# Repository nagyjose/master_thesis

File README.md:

# Diplomová práce – Systém kontrolních stanovišť a osobních jednotek pro orientační sporty

> Komplexní hardwarový a softwarový ekosystém pro měření mezičasů a bezdrátový přenos dat při orientačních a vytrvalostních závodech (orientační běh, MTBO, lyžařský orientační běh). Systém využívá časování a vzájemnou rádiovou komunikaci dle standardu **IEEE 802.15.4**, Bluetooth Low Energy (BLE) pro konfiguraci a servisní odečet, bezdrátové indukční nabíjení standardu Qi a vzdálený přenos mezičasů do závodního centra přes úzkopásmovou síť **NB-IoT** (Narrowband IoT).

**Autor:** Josef Nagy  
**Instituce:** České vysoké učení technické v Praze (Fakulta elektrotechnická)  
**Stav projektu:** Dokončeno a ověřeno (HW Revize 2.1 / FW v1.24) | **Licence:** Open Source / Akademické využití

---

## 1. Účel a řešený problém

Tradiční systémy pro orientační běh vyžadují fyzický kontakt čipu závodníka s kontrolní stanicí (kontaktní ražení) nebo využívají proprietární rádiové protokoly s omezeným dosahem a bez možnosti přímého online přenosu průběžných mezičasů z lesa do cílového prostoru.

Tento projekt přináší moderní modulární řešení:
1. **Základnová kontrolní stanice (Kontrola):** Stacionární jednotka umístěná na kontrolním bodě v terénu. Detekuje průchod závodníků bezkontaktně v rádiovém poli IEEE 802.15.4 (dosah 0.5 až 2 m), zaznamenává přesný čas průchodu s milisekundovou stabilitou (synchronizovaný krystal LSE) a odesílá mezičasy přes celulární síť NB-IoT na server pořadatele.
2. **Osobní jednotka závodníka (Závodník):** Kompaktní, lehká a odolná nositelná jednotka nošená běžcem na ruce, prstu či řídítkách kola. Při průchodu kontrolním bodem provede záznam do interní paměti a poskytne závodníkovi okamžitou akustickou (4 kHz piezo) a vizuální (LED) zpětnou vazbu.
3. **Výrobní a testovací infrastruktura:** Integrovaný technologický panel pro sériové SMT osazení (`production/`) a jehličkový programovací přípravek Bed-of-Nails (`testing/`) pro rychlé nahrání firmwaru a testování.
4. **Hermetické provedení pouzder:** 3D mechanické konstrukce krabiček (`mechanics/`) optimalizované pro venkovní použití s integrovaným Qi bezdrátovým nabíjením eliminujícím vnější konektory.

---

## 2. Systémová architektura

Následující diagram znázorňuje kompletní architekturu celého systému od detekce průběhu až po výrobu a testování:

```mermaid
flowchart TD
    subgraph Runner["🏃 Závodník na trati"]
        Z["Osobní jednotka Závodník<br/>(STM32WB55CGUx + Qi + Bzučák 4 kHz)"]
    end

    subgraph Checkpoint["🚩 Kontrolní stanoviště v terénu"]
        K["Kontrolní stanice Kontrola<br/>(STM32WB55RGVx + Quectel BC660K)"]
    end

    subgraph RF["📡 Bezdrátové rozhraní (RF 2.4 GHz)"]
        Z <== "1. Bezkontaktní detekce & časování<br/>(IEEE 802.15.4 / sub-ms handshake)" ==> K
        Z -. "Konfigurace & odečet (BLE 5.4)" .-> Mobile["Mobilní aplikace pořadatele"]
        K -. "Servisní diagnostika (BLE / USB)" .-> Mobile
    end

    subgraph Feedback["🔊 Zpětná vazba pro běžce"]
        Z --> BUZZ["Akustický bzučák 4 kHz + 💡 Záblesk LED"]
    end

    subgraph Cloud["☁️ Závodní centrum & Online výsledky"]
        K == "2. Online přenos mezičasů (NB-IoT)" ==> Server["Centrální závodní server & Live Tracking"]
        Server --> LiveWeb["Online výsledkový web pro diváky"]
        FinishUnit["Cílová čtečka závodníků"] -. "Vyčtení historie" .-> Server
    end

    subgraph Infrastructure["🏭 Výrobní a testovací infrastruktura (Monorepo DP)"]
        Panel["DP-Panel (production/)<br/>4vrstvý výrobní SMT panel pro JLCPCB"]
        Jig["DP-jigs (testing/)<br/>41pinový Bed-of-Nails testovací přípravek"]
        Mech["DP-Enclosure (mechanics/)<br/>Vodotěsná 3D pouzdra FreeCAD"]
        Panel -. "Vylomení osazených desek" .-> Jig
        Jig -. "Flash firmwaru & testování" .-> K
        Jig -. "Flash firmwaru & testování" .-> Z
        Mech -. "Zapouzdření desek" .-> K
        Mech -. "Zapouzdření desek" .-> Z
    end
```

---

## 3. Struktura repozitáře (Monorepo)

Repozitář sdružuje veškeré zdrojové kódy firmwaru, hardwarové návrhy desek, výrobní panelizaci, testovací přípravky i mechanické modely pouzder:

```text
DP/
├── hardware/
│   ├── DP-Kontrola/            # [PRJ-10] Zdrojový HW návrh kontrolní stanice (KiCad 8/9)
│   │   ├── DP-Kontrola.kicad_pro / kicad_sch / kicad_pcb
│   │   ├── MCU.kicad_sch, NB-IoT-module.kicad_sch, wireless-charger.kicad_sch
│   │   ├── DP-Kontrola-*.gbr / drl / dxf / step (Výrobní a 3D podklady)
│   │   └── README.md           # Podrobná technická dokumentace desky Kontrola
│   └── DP-Zavodnik/            # [PRJ-11] Zdrojový HW návrh osobní jednotky (KiCad 8/9)
│       ├── DP-Zavodnik.kicad_pro / kicad_sch / kicad_pcb
│       ├── MCU.kicad_sch, wireless-charger.kicad_sch, signaling.kicad_sch
│       ├── DP-Zavodnik-*.dxf / step / pdf (Výrobní a 3D podklady)
│       └── README.md           # Podrobná technická dokumentace desky Závodník
│
├── Kontrola_Syst/              # C / HAL Firmware stanice Kontrola (STM32CubeIDE)
│   ├── Core/                   # Aplikační logika (M4): main.c, app_entry.c, RTC, flash logger
│   ├── STM32_WPAN/             # Wireless middleware (M0+): BLE, 802.15.4 MAC, app_nbiot.c
│   ├── Drivers/                # CMSIS a STM32WBxx HAL drivery
│   └── Kontrola_Syst.ioc       # Projekt STM32CubeMX
│
├── Zavodnik_Syst/              # C / HAL Firmware jednotky Závodník (STM32CubeIDE)
│   ├── Core/                   # Aplikační logika (M4): stavový automat, bzučák 4 kHz, LPM
│   ├── STM32_WPAN/             # Bezdrátový zásobník IEEE 802.15.4 a BLE
│   ├── Drivers/                # CMSIS a STM32WBxx HAL drivery
│   └── Zavodnik_Syst.ioc       # Projekt STM32CubeMX
│
├── production/                 # [PRJ-12] Výrobní panelizace plošných spojů (DP-Panel)
│   ├── DP-Panel.kicad_pcb      # Sdružený 4vrstvý výrobní panel (114.05 × 77.55 mm)
│   ├── DP-Panel-job.gbrjob     # Gerber job s definicí stackupu Nan-Ya NP-155FR
│   ├── fab-data/               # Kompletní výrobní balíček (Gerber, BOM s LCSC ID, CPL)
│   └── README.md               # Dokumentace výrobního panelu pro SMT linku
│
├── testing/                    # [PRJ-13] Testovací a flashovací přípravek (DP-jigs)
│   ├── DP-jigs.kicad_pcb / sch # 2vrstvá deska Bed-of-Nails testeru
│   ├── fab-data/               # Výrobní data přípravku pro výrobu
│   └── README.md               # Dokumentace testeru a postup oživování
│
├── mechanics/                  # [PRJ-15] 3D konstrukce krabiček a pouzder (DP-Enclosure)
│   ├── DP-Kontrola.FCStd       # Parametrický 3D model krabičky Kontrola ve FreeCADu
│   ├── *.png                   # 15 fotorealistických renderů pohledů a řezů
│   └── README.md               # Návod na 3D tisk a montáž pouzder
│
├── .gitignore                  # Ochrana před commitem build artefaktů, záloh a cache
└── README.md                   # Tato hlavní přehledová dokumentace monorepa
```

---

## 4. Klíčové hardwarové komponenty a subsystémy

Obě jednotky sdílejí společnou architekturu postavenou na mikrokontrolérech STMicroelectronics a správě napájení Texas Instruments:

| Subsystém | Jednotka Kontrola | Jednotka Závodník |
| :--- | :--- | :--- |
| **Řídící mikrokontrolér** | **STM32WB55RGVx** (VFQFPN68)<br/>Dual Core Cortex-M4 + M0+ | **STM32WB55CGUx** (UFQFPN48)<br/>Kompaktní miniaturní pouzdro |
| **RF komunikace** | 2.4 GHz IEEE 802.15.4 & BLE 5.4,<br/>integrovaná PCB anténa | 2.4 GHz IEEE 802.15.4 & BLE 5.4,<br/>integrovaná PCB anténa |
| **Celulární telemetrie** | **Quectel BC660K-GL** (NB-IoT modem)<br/>externí anténa SMA / u.FL | *Není osazeno (přenos přes Kontrolu)* |
| **Bezdrátové nabíjení** | **TI BQ51013BRHLR** (Qi přijímač 5 W) | **TI BQ51013BRHLR** (Qi přijímač 5 W) |
| **Správa nabíjení & Power-Path** | **TI BQ24232RGTR** (až 500 mA) | **TI BQ24232RGTR** (přizpůsobeno Li-Po) |
| **Hlavní step-down měnič** | **TI TPS62842DGRR** ($I_Q \approx 60\text{ nA}$) | **TI TPS62842DGRR** ($I_Q \approx 60\text{ nA}$) |
| **Napájení modemu** | **TI TPS628502QDRLRQ1** (2 A buck) | *Není přítomno* |
| **Zpětná vazba pro uživatele** | RGB stavové LED, bzučák, USB CDC | Vysoce svítivé LED, 4 kHz piezo driver |
| **Deska plošných spojů** | 4 vrstvy FR4, ENIG zlacení | 4 vrstvy FR4, zaoblený nositelný tvar |

---

## 5. Softwarová architektura a bezdrátový zásobník

Firmware běží na dvoujádrovém mikrokontroléru řady STM32WB:
- **CPU1 (ARM Cortex-M4 @ 64 MHz):** Běh uživatelské aplikace, sekvencer událostí `UTIL_SEQ`, obsluha RTC časovače, správa energetických režimů (Sleep/Stop mode), zápis do Flash paměti (`flash_logger.c`), řízení NB-IoT FIFO fronty a USB komunikace.
- **CPU2 (ARM Cortex-M0+ @ 32 MHz):** Vyhrazený bezdrátový koprocesor. Vyžaduje nahrání binárního firmwaru ST `stm32wb5x_Ble_Mac_802_15_4_fw.bin`. Zajišťuje bezdrátovou obsluhu na nejnižší vrstvě PHY/MAC v reálném čase bez zatížení aplikačního jádra.
- **Mezijádrová komunikace:** Realizována pomocí hardwarového řadiče IPCC (Inter-Processor Communication Controller) a sdílené paměti RAM.

---

## 6. Návod na zprovoznění a vývoj

### A. Vývoj a úprava hardwaru (KiCad)
1. Nainstalujte **KiCad EDA v8.0** nebo novější (testováno i na KiCad 9).
2. Otevřete projekt `hardware/DP-Kontrola/DP-Kontrola.kicad_pro` nebo `hardware/DP-Zavodnik/DP-Zavodnik.kicad_pro`.
3. Všechny knihovny symbolů a footprintů jsou uloženy v projektu nebo odpovídají standardní KiCad knihovně.
4. Výrobní Gerbery a vrtací podklady jsou vygenerovány ve složkách jednotlivých desek a v modulu `production/`.

### B. Překlad firmwaru (STM32CubeIDE)
1. Otevřete **STM32CubeIDE** (testováno na verzi 1.15+).
2. Zvolte `File -> Import... -> Existing Projects into Workspace` a načtěte složky `Kontrola_Syst` a `Zavodnik_Syst`.
3. Před prvním spuštěním nového mikrokontroléru nahrajte do koprocesoru bezdrátový zásobník:
   - Spusťte nástroj **STM32CubeProgrammer**.
   - Připojte desku přes programátor ST-LINK (SWD rozhraní na testovacím přípravku `testing/`).
   - Přejděte na záložku *Firmware Upgrade* a nahrajte binárku `stm32wb5x_Ble_Mac_802_15_4_fw.bin` na vyhrazenou adresu bezdrátového subsystému.
4. Zkompilujte projekt v konfiguraci `Release` nebo `Debug` a nahrajte jej do mikrokontroléru.

### C. Mechanická pouzdra a 3D konstrukce (mechanics/)

Modul `mechanics/` obsahuje kompletní 3D mechanické řešení pouzder a krabiček vyvinutých pro obě jednotky časoměrného systému:

| Pouzdro kontrolní stanice Kontrola | Pouzdro osobní jednotky Závodník |
| :---: | :---: |
|  |  |

Podrobné informace a kompletní fotogalerii viz [mechanics/README.md](file:///c:/Users/josef/Documents/KiCad-projects/DP/mechanics/README.md).

### D. Výrobní panelizace a podklady pro osazení (production/)

Sdružený 4vrstvý technologický panel spojující desky Kontrola a Závodník pro sériové osazování na SMT lince (JLCPCB):

| 3D render výrobního panelu shora | Výrobní layout vrstvy Top Copper (F.Cu) |
| :---: | :---: |
|  |  |

Podrobné informace, vrstvy a kusovník viz [production/README.md](file:///c:/Users/josef/Documents/KiCad-projects/DP/production/README.md).

### E. Programovací a testovací přípravek (testing/)

Dvouvrstvý Bed-of-Nails tester s 41 pružinovými kontakty a rozhraním IDC 2×22 pro oživování, diagnostiku a programování obou desek:

| Schéma zapojení testovacího přípravku | 3D render osazeného testeru Bed-of-Nails |
| :---: | :---: |
|  |  |

Podrobné informace, schéma a montážní výkres viz [testing/README.md](file:///c:/Users/josef/Documents/KiCad-projects/DP/testing/README.md).

---

## 7. Návaznost modulů v rámci diplomové práce

- **PRJ-10 (DP-Kontrola):** Integrováno ve složce `hardware/DP-Kontrola/`.
- **PRJ-11 (DP-Zavodnik):** Integrováno ve složce `hardware/DP-Zavodnik/`.
- **PRJ-12 (DP-Panel):** Integrováno ve složce `production/`.
- **PRJ-13 (DP-jigs):** Integrováno ve složce `testing/`.
- **PRJ-14 (DP-Frame):** Vyřazeno / nepublikováno (prázdná šablona bez zapojení a DPS).
- **PRJ-15 (DP-Enclosure):** Integrováno ve složce `mechanics/`.
- **PRJ-16 (DP-Merge):** Vyřazeno / nepublikováno (prázdná schránka).

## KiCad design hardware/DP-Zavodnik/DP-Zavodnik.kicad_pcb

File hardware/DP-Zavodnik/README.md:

# DP-Zavodnik – Hardwarová osobní jednotka závodníka

> Hardwarový návrh kompaktní 4vrstvé desky plošných spojů osobní jednotky pro bezkontaktní časomíru orientačních sportů (nositelné zařízení na ruku, prst či řídítka kola) s mikrokontrolérem STM32WB55, integrovanou RF anténou 2.4 GHz (IEEE 802.15.4 / BLE), akusticko-optickou odezvou a bezdrátovým Qi nabíjením.

**Stav projektu:** Dokončeno (HW Revize 1.0) | **Hlavní technologie:** KiCad 8/9, STM32WB55CGUx (UFQFPN48, Dual-core ARM Cortex-M4 + M0+), Texas Instruments Power Management (BQ51013B, BQ24232, TPS62842)

---

## 1. Účel a funkce

Projekt **DP-Zavodnik** představuje osobní mobilní jednotku (obdoba moderního elektronického čipu SI-Card / SIAC) v systému bezkontaktní časomíry pro orientační sporty. Závodník jednotku nese během celého závodu upevněnou na prstu, zápěstí nebo na rámu kola (MTBO). 

Hlavní funkce zařízení:
- **Bezkontaktní ražení kontrol (Air Punching):** Automatická detekce kontrolního stanoviště [DP-Kontrola](../DP-Kontrola) při průběhu v rádiovém dosahu pomocí standardu IEEE 802.15.4 bez nutnosti fyzického zasouvání čipu do otvoru.
- **Okamžitá odezva (Feedback):** Výkonný akustický bzučák buzený signálem 4 kHz a vysoce svítivé LED diody dávají závodníkovi v plném běhu okamžité a zřetelné potvrzení úspěšného zaznamenání kontrolního bodu.
- **Nenulová paměť závodu:** Ukládání identifikačních kódů kontrol a přesných časů oražení do interní paměti mikrokontroléru pro následné vyčtení v cílovém prostoru.
- **Ergonomická nositelná konstrukce:** Zaoblený tvar desky přizpůsobený tělu závodníka a integraci do kompaktního pouzdra [DP-Enclosure](../../mechanics).
- **Hermetické provedení a Qi nabíjení:** Zařízení nemá vnější kontakty podléhající oxidaci a znečištění blátem či potem; nabíjení vestavěného Li-Po článku probíhá bezdrátově přes standard Qi.

---

## 2. Architektura a blokové schéma

Schéma zapojení je optimalizováno pro minimální rozměry, nízkou hmotnost a maximální výdrž na jedno nabití.

```mermaid
flowchart TD
    subgraph Power["⚡ Napájecí subsystém"]
        Qi["Bezdrátové Qi nabíjení<br/>(TI BQ51013B)"] -->|5V rect| BQ["Li-Po Charger & Power Path<br/>(TI BQ24232)"]
        USB["USB rozhraní<br/>(Servis / nouzové nabíjení)"] --> BQ
        BAT["Li-Po akumulátor<br/>(3.7V jednocelový)"] <--> BQ
        BQ -->|VSYS| REG["Ultra-Low-Iq Buck 3.3V<br/>(TI TPS62842, Iq=60nA)"]
    end

    subgraph Core["🧠 Řídící & RF jádro"]
        REG --> MCU["STM32WB55CGUx<br/>(UFQFPN48, Dual-core<br/>Cortex-M4 + Cortex-M0+)"]
        MCU <--> RF_ANT["Integrovaná PCB anténa 2.4 GHz<br/>(IEEE 802.15.4 / BLE)"]
        MCU --> RTC["RTC krystal 32.768 kHz (LSE)"]
        MCU --> HSE["Vysokofrekvenční krystal 32 MHz (HSE)"]
    end

    subgraph UserFeedback["🔊 Signalizace a odezva"]
        MCU -->|PWM 4 kHz driver| BUZZ["Piezoelektrický bzučák<br/>(Akustické potvrzení oražení)"]
        MCU --> LEDS["Optická LED indikace<br/>(Zelená / Červená / Modrá)"]
        BAT -.->|ADC monitor| MCU
    end
```

---

## 3. Hardware, schéma a PCB

### 3.1 3D vizualizace osobní jednotky

### 3.2 Schéma zapojení

<details>
<summary>🔍 Zobrazit detailní listy schématu zapojení (strany 2–4)</summary>

#### List 2: Mikrokontrolér STM32WB55CGUx, oscilátory a RF výstup

#### List 3: Qi bezdrátové nabíjení (BQ51013B) a Power-Path správa baterie (BQ24232)

#### List 4: Budicí obvod 4 kHz piezo bzučáku, stavové LED a monitorování akumulátoru

</details>

📄 [Otevřít kompletní schéma v plném rozlišení (vektorové PDF)](DP-Zavodnik-Schema.pdf)

### 3.3 Návrh a layout plošného spoje (PCB Layout)

<details>
<summary>🔍 Zobrazit výkresy jednotlivých vrstev a technologických masek</summary>

| Vrstva / Náhled | Soubor |
| :--- | :--- |
| **Top strana (F.Cu + Silk + Mask)** |  |
| **Vnitřní vrstva In1 (GND / Power)** |  |
| **Vnitřní vrstva In2 (Signály)** |  |
| **Bottom strana (B.Cu)** |  |
| **Pájecí maska a potisk** |  |
| **Vrtací plán (Drill drawing)** |  |
| **Kompletní montážní výkres** |  |

</details>

📄 [Otevřít kompletní výrobní výkres vrstev v plném rozlišení (vektorové PDF)](DP-Zavodnik-Layout.pdf)

---

## 4. Struktura projektu

```text
DP-Zavodnik/
├── docs/
│   └── images/                 # Exportované grafické náhledy schémat, vrstev layoutu a 3D rendery
│       ├── pcb_3d_render.png   # 3D fotorealistický render osazené jednotky
│       ├── pcb_layout*.png     # Náhledy vrstev a masek plošného spoje
│       └── schematic_p*.png    # Náhledy všech 4 listů schématu
├── DP-Zavodnik.kicad_pro       # Hlavní projektový soubor KiCad
├── DP-Zavodnik.kicad_sch       # Kořenové schéma (Sheet 1)
├── MCU.kicad_sch               # Schéma zapojení mikrokontroléru STM32WB55CGUx (Sheet 2)
├── wireless-charger.kicad_sch  # Schéma Qi bezdrátového nabíjení a Power-Path (Sheet 3)
├── signaling.kicad_sch         # Schéma driveru bzučáku, LED diod a měření baterie (Sheet 4)
├── DP-Zavodnik.kicad_pcb       # 4vrstvá deska plošných spojů s optimalizovaným tvarem
├── DP-Zavodnik-Base.step       # 3D STEP model spodní části desky
├── DP-Zavodnik-Lid.step        # 3D STEP model krytu/sestavy
├── DP-Zavodnik-Layout.pdf      # Výrobní výkres vrstev DPS v PDF
├── DP-Zavodnik-Schema.pdf      # Vektorové schéma v PDF
├── DP-Zavodnik-*.dxf           # Exporty vrstev do formátu DXF pro mechanickou konstrukci
├── DP-Zavodnik-view-*.png      # Fotorealistické 3D rendery osazené desky
└── .gitignore                  # Ochrana před zálohami, kolizními soubory a cache KiCadu
```

---

## 5. Technické parametry hardwaru

| Parametr | Hodnota / Specifikace |
| :--- | :--- |
| **Rozměry a tvar** | Miniaturní zaoblená deska optimalizovaná pro tělo sportovce |
| **Počet vrstev** | 4 vrstvy (Top Signal, In1 Power/GND, In2 Signal, Bottom Signal) |
| **Materiál a tloušťka** | FR4, 1.6 mm, povrchová úprava ENIG (zlacení) |
| **Mikrokontrolér** | **STM32WB55CGUx** (UFQFPN48, dual-core Cortex-M4 @ 64 MHz + Cortex-M0+ pro RF) |
| **RF rozhraní 2.4 GHz** | Integrovaná mikropásková anténa, LC filtr, IEEE 802.15.4 & BLE 5.4 |
| **Bezdrátové nabíjení** | **TI BQ51013BRHLR** – certifikovaný přijímač Qi standardu |
| **Správa napájení a nabíjení** | **TI BQ24232RGTR** – lineární nabíječ s dynamickým řízením napájení |
| **Step-down napájení** | **TI TPS62842DGRR** – ultra-low IQ měnič pro maximalizaci výdrže akumulátoru |
| **Akustická odezva** | Piezo měnič řízený diskrétním MOSFET budičem na rezonanční frekvenci 4 kHz |
| **Optická odezva** | Vysoce svítivé signalizační LED diody |
| **Napájení** | Integrovaný miniaturní Li-Po článek (3.7 V) |

---

## 6. Požadavky a otevření projektu

- **KiCad EDA:** Doporučena verze **8.0** nebo novější (projekt vytvořen a verifikován v KiCad 8/9).
- Pro otevření projektu spusťte `DP-Zavodnik.kicad_pro` v KiCadu.
- Výrobní předlohy jednotlivých vrstev jsou k dispozici v souborech `DP-Zavodnik-Layout.pdf` a DXF exportech.
- Pro návrh plastové krabičky a montážních prvků použijte 3D STEP modely `DP-Zavodnik-Base.step` a `DP-Zavodnik-Lid.step`.

---

## 7. Vazby na další projekty

- **[DP-Kontrola](../DP-Kontrola) (PRJ-10):** Základnová stacionární stanice, která zaznamenává průchod této jednotky.
- **[DP Monorepo](https://github.com/nagyjose/DP):** Centrální repozitář obsahující firmware `Zavodnik_Syst` a `Kontrola_Syst`.
- **[DP-Panel](../../production) (PRJ-12):** Společná panelizace s deskou Kontrola pro hromadné osazování.
- **[DP-jigs](../../testing) (PRJ-13):** Testovací a flashovací přípravek pro nahrání firmwaru na výrobní lince.
- **[DP-Enclosure](../../mechanics) (PRJ-15):** 3D model pouzdra navržený ve FreeCADu.

---

## 8. Stav projektu a historie

- **Verze 1.0 (Diplomová práce - Finální):** Kompletně navržený hardware, vyrobené prototypové desky, ověřena funkčnost bezdrátového nabíjení, 4 kHz bzučáku i oboustranné rádiové komunikace 802.15.4 s jednotkou Kontrola.

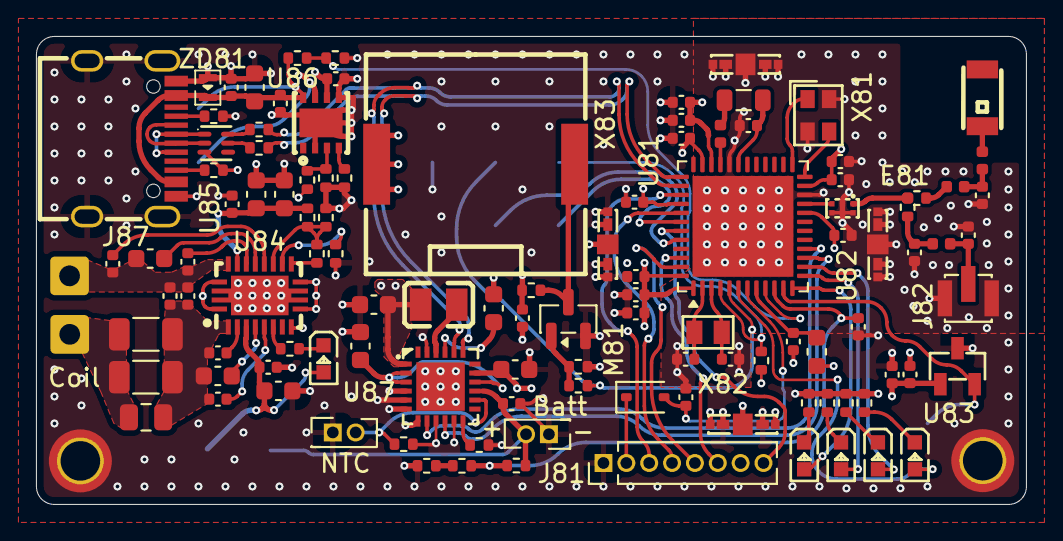
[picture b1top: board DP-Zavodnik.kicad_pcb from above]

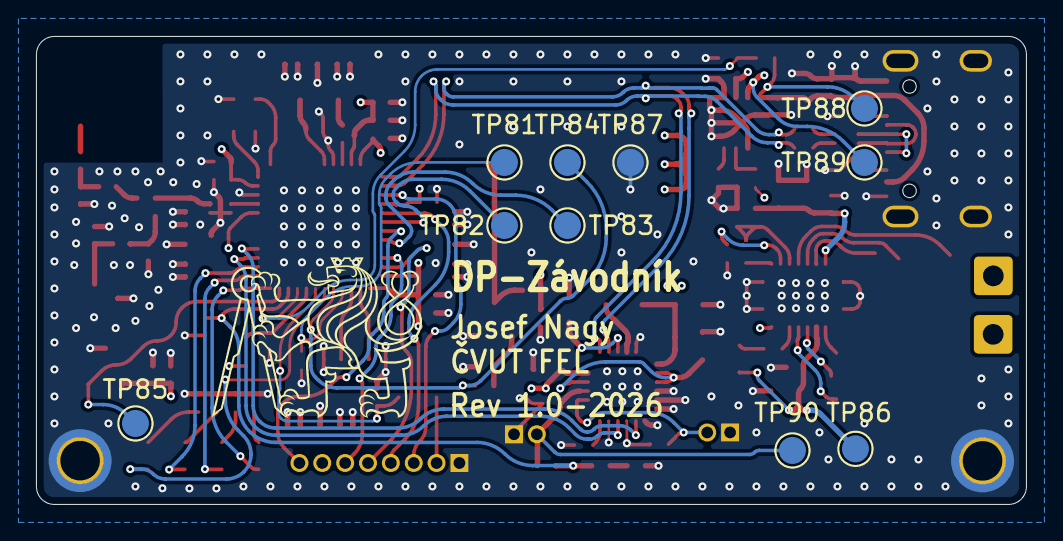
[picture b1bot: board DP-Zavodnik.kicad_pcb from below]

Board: 4 copper layers, 55.0 x 26.0 mm, 125 parts (10 on the bottom side), 78 nets.

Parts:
C81, C84, C86, C87, C88, C90, C92, C93, C95, C99, C100, C102, C114, C116, C121, C122: 100n; C_0402_1005Metric
C82, C83, C85, C101: 4.7u; C_0402_1005Metric
C89, C119: 100p; C_0402_1005Metric
C91, C94: 7.5p; C_0402_1005Metric
C96, C97, C98: N.C.; C_0402_1005Metric
C103: C_0805_2012Metric
C104, C105: 39n; C_1206_3216Metric
C106: 910p; C_0402_1005Metric
C107: C_0402_1005Metric
C108, C113: 470n; C_0603_1608Metric
C109, C112: 22n; C_0402_1005Metric
C110, C111: 10n; C_0402_1005Metric
C115, C117, C118, C124, C125, C126: 10u; C_0603_1608Metric
C120: 4.7u; C_0603_1608Metric
C123: 1u; C_0402_1005Metric
C127: 2.2u; C_0603_1608Metric
D81: 1N5819WS; D_SOD-323
E81: 2450AT18B100E; ANT-SMD_L3.2-W1.6
FB81: BLM18AG601SN1D; L_0603_1608Metric
H81, H82: MountingHole_Pad; MountingHole_2.2mm_M2_ISO7380_Pad_TopBottom
J81: Conn_01x08; PinHeader_1x08_P1.27mm_Vertical
J82: CONUFL001-SMD-T; IPEX-SMD_3P-L2.6-W2.6-LS3.0
J85, J86: SolderWire-0.5sqmm_1x01_D0.9mm_OD2.1mm
J87: TYPE-C-31-M-12; USB-C_SMD-TYPE-C-31-M-12_1
J88, J90: Conn_01x02; PinHeader_2x01_P1.27mm_Vertical
L81: 10n; L_0402_1005Metric
L82: 10u; L_0805_2012Metric
L83, L84, L85: 0R; L_0402_1005Metric
L87: 2.2u; L0806
LED81: VLMO1300-GS08; LED0603-RD_BLUE
LED82: VLMS1300-GS08; LED0603-RD_BLUE
LED83: VLMG1300-GS08; LED0603-RD_BLUE
LED84, LED85: VLMB1300-GS08; LED0603-RD_BLUE
M81: 2N7002; SOT-23
R81, R85, R97, R109: 10k; R_0402_1005Metric
R82, R83, R103, R104: 0R; R_0402_1005Metric
R84: 100R; R_0402_1005Metric
R86, R96: 1k; R_0402_1005Metric
R87, R88, R89: 1M; R_0402_1005Metric
R90, R91, R105: 100k; R_0402_1005Metric
R92, R93, R94, R95: 200R; R_0402_1005Metric
R98: 1.37k; R_0402_1005Metric
R99: 20k; R_0402_1005Metric
R100: 196R; R_0402_1005Metric
R101, R102: 5.1k; R_0402_1005Metric
R106: 22k; R_0402_1005Metric
R107: 470R; R_0402_1005Metric
R108: 4.7k; R_0402_1005Metric
SC81, SC82, SC83, SC84: S0951-46R; SMD_S0951-46R_1
TP81, TP82, TP83, TP84, TP85, TP86, TP87, TP88, TP89, TP90: TestPoint_Pad_D1.5mm
U81: STM32WB55CGUx; QFN-48-1EP_7x7mm_P0.5mm_EP5.6x5.6mm
U82: MLPF-WB55-01E3; FILTER-SMD_6P-L1.6-W1.0-P0.50-BL
U83: DRV5032FADBZR; SOT-23-3_L2.9-W1.3-P0.95-LS2.4-BR
U84: BQ51013BRHLR; VQFN-20_L4.5-W3.5-P0.50-BL-EP_BQ24100RHLR
U85: ECMF02-2AMX6; UFQFN-6_L1.7-W1.5
U86: TPS2113ADRBR; SON-8_L3.0-W3.0-P0.65-LS3.0-BL-EP
U87: NPM1100-QDAA-R7; VQFN-24_L4.0-W4.0-P0.50-TL-EP2.7
X81: NX2016SA-32MHZ-STD-CZS-5; OSC-SMD_4P-L2.0-W1.6-BL
X82: NX2012SA-32_768KHZ-EXS00A-MU00527; CRYSTAL-SMD_L2.0-W1.2
X83: PKLCS1212E4001-R1; BUZ-SMD_2P-L12.0-W12.0-L_PKLCS1212E4001-R1
ZD81: ESDA7P60-1U1M; D1610-RD

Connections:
+3V3: C83.1, C84.1, C85.1, C86.1, C87.1, C88.1, C89.1, C90.1, C92.1, C93.1, C100.1, C101.1, C102.1, C124.1, FB81.1, J81.7, L87.1, R86.2, U81.1 (VBAT), U81.20 (VDD), U81.23 (VDDRF), U81.34 (VDDSMPS), U81.35 (VDD), U81.40 (VDDUSB), U81.48 (VDD), U83.1 (VCC), U87.1 (VOUTB), X83.1 (+)
+5VD: C127.1, TP89.1, U86.7 (OUT), U87.17 (VBUS)
+5VL: C114.1, C115.1, C122.1, LED85.2 (+), TP86.1, U84.4 (OUT), U86.6 (IN2)
+5VP: C119.1, C120.1, C121.1, J87.A4B9 (VBUS), J87.B4A9 (VBUS), R90.2, R105.2, TP88.1, U84.9 (AD), U86.8 (IN1), ZD81.1 (C)
/BLE-RF/rf1: R82.1, R83.1, U82.1 (OUT)
/BLE-RF/rf2: L83.1, R82.2
/BLE-RF/rf3: C97.1, L83.2, L85.1
/BLE-RF/rf4: E81.1 (FEED), L85.2
/BLE-RF/rf5: C96.1, L84.1, R83.2
/BLE-RF/rf6: C98.1, J82.1, L84.2
/MCU/nrst: D81.1 (K), J81.2
/MCU/smps: L81.1, L82.2
/power-management/USB-plug/cc1: J87.A5 (CC1), R101.2
/power-management/USB-plug/cc2: J87.B5 (CC2), R102.2
/power-management/USB-plug/d1n: J87.A7 (DN1), J87.B7 (DN2), U85.2 (D-)
/power-management/USB-plug/d1p: J87.A6 (DP1), J87.B6 (DP2), U85.1 (D+)
/power-management/USB-plug/d2n: R104.1, U85.5 (D-)
/power-management/USB-plug/d2p: R103.1, U85.6 (D+)
/power-management/power-switch/ilim2: R107.2, U86.4 (ILIM)
/power-management/power-switch/vsns: R105.1, R106.2, U86.3 (VSNS)
/power-management/regulator/dec: C126.1, U87.21 (DEC)
/power-management/regulator/ichg: R108.2, U87.12 (ICHG)
/power-management/regulator/sw: L87.2, U87.22 (SW)
/power-management/regulator/vsys: C125.1, U87.2 (VOUTBSET1), U87.3 (VOUTBSET0), U87.16 (VSYS)
/power-management/wireless-charger/ac1a: C103.1, C104.1, C105.1, J85.1
/power-management/wireless-charger/fod: R98.1, R99.1, R100.1, U84.14 (FOD)
/power-management/wireless-charger/ilim: R98.2, U84.12 (ILIM)
/power-management/wireless-charger/led5: LED85.1 (-), R96.2
/power-management/wireless-charger/led6: R96.1, U84.7 (/CHG)
/power-management/wireless-charger/rect: C116.1, C117.1, C118.1, R99.2, U84.18 (RECT)
/power-management/wireless-charger/ts: R97.2, U84.13 (TS/CTRL)
/signaling/bz1: M81.1 (G), R84.1, R85.2
/signaling/bz2: M81.3 (D), R86.1, X83.2 (-)
/signaling/led1: LED81.1 (-), R92.2
/signaling/led2: LED82.1 (-), R93.2
/signaling/led3: LED83.1 (-), R94.2
/signaling/led4: LED84.1 (-), R95.2
/signaling/meas: R88.1, R89.2
AC1: C103.2, C104.2, C105.2, C106.1, C107.1, C108.1, C109.1, C110.1, U84.2 (AC1)
AC2: C106.2, C107.2, C111.1, C112.1, C113.1, J86.1, U84.19 (AC2)
BATT_MEAS: C99.1, R87.1, R88.2, U81.10 (ADC1_IN6)
BOOT1: C110.2, U84.3 (BOOT1)
BOOT2: C111.2, U84.17 (BOOT2)
CLAMP1: C108.2, U84.5 (CLMP1)
CLAMP2: C113.2, U84.16 (CLMP2)
COMM1: C109.2, U84.6 (COM1)
COMM2: C112.2, U84.15 (COM2)
GND: C81.2, C82.2, C83.2, C84.2, C85.2, C86.2, C87.2, C88.2, C89.2, C90.2, C91.2, C92.2, C93.2, C94.2, C95.2, C96.2, C97.2, C98.2, C99.2, C100.2, C101.2, C102.2, C114.2, C115.2, C116.2, C117.2, C118.2, C119.2, C120.2, C121.2, C122.2, C123.2, C124.2, C125.2, C126.2, C127.2, H81.1, H82.1, J81.1, J82.2, J82.3, J87.1 (EH), J87.2 (EH), J87.3 (EH), J87.4 (EH), J87.A1B12 (GND), J87.B1A12 (GND), J88.1, J90.1, M81.2 (S), R81.2, R85.1, R89.1, R91.1, R92.1, R93.1, R94.1, R95.1, R97.1, R100.2, R101.1, R102.1, R106.1, R107.1, R108.1, R109.1, SC81.1, SC81.2, SC81.3, SC81.4, SC81.5, SC82.1, SC82.2, SC82.3, SC82.4, SC82.5, SC83.1, SC83.2, SC83.3, SC83.4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
HAL_WKUP: TP85.1, U81.11 (SYS_WKUP4), U83.2 (OUT)
SIG_Blink: LED81.2 (+), U81.6 (PB9)
SIG_Buzzer: R84.2, TP84.1, U81.5 (TIM16_CH1)
SIG_LED1: LED82.2 (+), U81.12 (PA3)
SIG_LED2: LED83.2 (+), U81.13 (PA4)
SIG_LED3: LED84.2 (+), U81.14 (PA5)
SRM32_JTRST: TP83.1, U81.44 (SYS_JTRST)
STM32_BOOT0: R81.1, TP81.1, U81.4 (PH3)
STM32_DN: R104.2, U81.37 (USB_DM), U87.19 (D-)
STM32_DP: R103.2, U81.38 (USB_DP), U87.20 (D+)
STM32_JTDI: TP82.1, U81.42 (SYS_JTDI)
STM32_JTDO: J81.8, U81.43 (SYS_JTDO-SWO)
STM32_NRST: C81.1, D81.2 (A), U81.7 (NRST)
STM32_OSC32_IN: C91.1, U81.2 (RCC_OSC32_IN), X82.1 (OSC1)
STM32_OSC32_OUT: C94.1, U81.3 (RCC_OSC32_OUT), X82.2 (OSC2)
STM32_OSC_IN: U81.25 (OSC_IN), X81.1
STM32_OSC_OUT: U81.24 (OSC_OUT), X81.3
STM32_RF1: U81.21 (RF1), U82.3 (IN)
STM32_RX: J81.5, U81.47 (USART1_RX)
STM32_SMPS_FB: C82.1, L82.1, U81.31 (VFBSMPS)
STM32_SMPS_LX: L81.2, U81.33 (VLXSMPS)
STM32_SWCLK: J81.4, U81.41 (SYS_JTCK-SWCLK)
STM32_SWDIO: J81.3, U81.39 (SYS_JTMS-SWDIO)
STM32_TX: J81.6, U81.46 (USART1_TX)
USB_TRIG: R90.1, R91.2, U81.9 (SYS_WKUP1)
VBAT: C123.1, J88.2, R87.2, TP90.1, U87.15 (VBAT)
VDDA: C95.1, FB81.2, U81.8 (VDDA)
nPM_CHG: U81.16 (PA7), U87.8 (CHG)
nPM_ERR: U81.15 (PA6), U87.10 (ERR)
nPM_NTC: J90.2, R109.2, U87.14 (NTC)

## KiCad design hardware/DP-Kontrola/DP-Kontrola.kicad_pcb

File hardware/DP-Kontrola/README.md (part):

# DP-Kontrola – Hardwarová základnová jednotka časomíry

> Hardwarový návrh 4vrstvé desky plošných spojů stacionární kontrolní stanice pro bezkontaktní časomíru orientačního běhu s dvoujádrovým bezdrátovým mikrokontrolérem STM32WB55, integrovanou RF anténou 2.4 GHz, NB-IoT konektivitou pro online přenos mezičasů do centra závodu a bezdrátovým Qi nabíjením.

**Stav projektu:** Dokončeno (HW Revize 2.1) | **Hlavní technologie:** KiCad 8/9, STM32WB55RGV6 (Dual-core ARM Cortex-M4 + M0+), Quectel BC660K-GL (NB-IoT), Texas Instruments Power Management (BQ51013B, BQ24232, TPS62842)

---

## 1. Účel a funkce

Projekt **DP-Kontrola** tvoří základnovou (stacionární) stanici komplexního systému bezkontaktní časomíry pro orientační sporty (orientační běh, MTBO, běh na lyžích). Stanice je umístěna v terénu na kontrolním stanovišti (lampionu) a plní následující funkce:

- **Bezkontaktní detekce závodníka:** Využívá radiové rozhraní 2.4 GHz na protokolu IEEE 802.15.4 a Bluetooth Low Energy (BLE) pro spolehlivou registraci průběhu závodníka s osobní jednotkou [DP-Zavodnik](../DP-Zavodnik).
- **Přesné měření času:** Synchronizovaný vnitřní RTC obvod s teplotně kompenzovaným krystalem LSE zajišťuje záznam času průchodu s milisekundovou přesností.
- **Online přenos mezičasů (NB-IoT):** Integrovaný celulární modul Quectel BC660K-GL odesílá průchody závodníků v reálném čase přes úzkopásmovou síť IoT do centrálního vyhodnocovacího systému.
- **Autonomní napájení a bezdrátové nabíjení:** Možnost dobíjení Li-Ion/Li-Po článku bez nutnosti otevírání vodotěsné krabičky prostřednictvím bezdrátového Qi rozhraní (5 W) nebo USB-C konektoru s automatickým řízením napájecí cesty (Power Path).
- **Offline záznam a bezpečnost dat:** Zálohování všech oražení do interní Flash paměti pro případ výpadku mobilního signálu v hlubokém lese.

---

## 2. Architektura a blokové schéma

Deska je navržena s důrazem na minimální klidovou spotřebu energie v terénu a vysokou spolehlivost radiového přenosu.

```mermaid
flowchart TD
    subgraph Power["⚡ Napájecí subsystém"]
        Qi["Bezdrátové Qi nabíjení<br/>(TI BQ51013B)"] -->|5V rect| BQ["Li-Ion Charger & Power Path<br/>(TI BQ24232)"]
        USB["USB-C konektor<br/>(5V VBUS)"] --> BQ
        BAT["Li-Ion / Li-Po akumulátor<br/>(3.7V nom)"] <--> BQ
        BQ -->|VSYS| REG_MCU["Ultra-Low-Iq Buck 3.3V<br/>(TI TPS62842, Iq=60nA)"]
        BQ -->|VSYS| REG_NBIOT["High-Current Buck 3.8V<br/>(TI TPS628502)"]
    end

    subgraph Core["🧠 Řídící & RF jádro"]
        REG_MCU --> MCU["STM32WB55RGVx<br/>(ARM Cortex-M4 @ 64MHz<br/>+ Cortex-M0+ pro RF)"]
        MCU <--> RF_ANT["Integrovaná PCB anténa 2.4 GHz<br/>(IEEE 802.15.4 / BLE)"]
        MCU --> RTC["RTC krystal 32.768 kHz (LSE)"]
        MCU <--> USB_DATA["USB 2.0 FS rozhraní<br/>(CDC konfigurace)"]
    end

    subgraph Peripherals["📡 Periferie a telemetrie"]
        REG_NBIOT --> NBIOT["Quectel BC660K-GL<br/>(NB-IoT modem)"]
        MCU <-->|UART + Ri / Wakeup| NBIOT
        NBIOT --> ANT_NBIOT["NB-IoT anténní konektor (u.FL / SMA)"]
        MCU --> LEDS["Optická signalizace (RGB LED)"]
        MCU --> BUZZ["Akustický bzučák"]
        BAT -.->|Dělič napětí / ADC| MCU
    end
```

---

## 3. Hardware, schéma a PCB

### 3.1 3D vizualizace a osazení desky

### 3.2 Schéma zapojení

<details>
<summary>🔍 Zobrazit detailní listy schématu zapojení (strany 2–5)</summary>

#### List 2: Mikrokontrolér STM32WB55, krystaly HSE/LSE a USB

#### List 3: Celulární modem Quectel BC660K-GL a SIM slot

#### List 4: Bezdrátové Qi nabíjení (BQ51013B) a nabíječ baterie (BQ24232)

#### List 5: Signalizace (RGB LED, bzučák) a monitorování napětí baterie

</details>

📄 [Otevřít kompletní schéma v plném rozlišení (vektorové PDF)](DP-Kontrola-Schema.pdf)

### 3.3 Návrh plošného spoje (PCB Layout)

📄 [Otevřít výrobní dokumentaci DPS v plném rozlišení (vektorové PDF)](DP-Kontrola.pdf)

---

## 4. Struktura projektu

```text
DP-Kontrola/
├── docs/
│   └── images/                 # Exportované grafické náhledy schémat, layoutu a 3D rendery
│       ├── pcb_3d_render.png   # 3D fotorealistický render osazené desky
│       ├── pcb_layout.png      # Náhled vrstev plošného spoje
│       └── schematic_p*.png    # Náhledy všech 5 listů schématu
├── DP-Kontrola.kicad_pro       # Hlavní projektový soubor KiCad
├── DP-Kontrola.kicad_sch       # Kořenové schéma (Sheet 1)
├── MCU.kicad_sch               # Schéma MCU části, hodin a krystalů (Sheet 2)
├── NB-IoT-module.kicad_sch     # Schéma modemu Quectel BC660K-GL a SIM slotu (Sheet 3)
├── wireless-charger.kicad_sch  # Schéma Qi cívky, BQ51013B a BQ24232 (Sheet 4)
├── signaling.kicad_sch         # Schéma LED indikace, bzučáku a monitoru baterie (Sheet 5)
├── DP-Kontrola.kicad_pcb       # 4vrstvá deska plošných spojů
├── DP-Kontrola-base.step       # 3D STEP model spodní části desky
├── DP-Kontrola-lid.step        # 3D STEP model krytu/sestavy
├── DP-Kontrola.pdf             # Kompletní výrobní dokumentace v PDF
├── DP-Kontrola-Schema.pdf      # Všechny listy schématu ve vektorovém PDF
├── DP-Kontrola-Layout-*.pdf    # Výkresy jednotlivých vrstev DPS
├── DP-Kontrola-*.dxf           # Exporty vrstev do formátu DXF pro mechanickou konstrukci
├── DP-Kontrola-*.gbr / drl     # Výrobní Gerbery a vrtací data (drill)
├── DP-Kontrola-view-*.png      # 3D fotorealistické rendery osazené desky
└── .gitignore                  # Ochrana před zálohami a cache soubory KiCadu
```

---

## 5. Technické parametry hardwaru

| Parametr | Hodnota / Specifikace |
| :--- | :--- |
| **Rozměry DPS** | Kompaktní tvar přizpůsobený skříňce [DP-Enclosure](../../mechanics) |
| **Počet vrstev** | 4 vrstvy (Top Signal, In1 Power/GND, In2 Signal, Bottom Signal) |
| **Materiál a tloušťka** | FR4, 1.6 mm, povrchová úprava ENIG (zlacení) |
| **Mikrokontrolér** | **STM32WB55RGVx** (VFQFPN68, dual-core Cortex-M4 + Cortex-M0+) |
| **RF rozhraní 2.4 GHz** | Integrovaná mikropásková anténa, LC přizpůsobovací obvod, IEEE 802.15.4 & BLE 5.4 |
| **Celulární konektivita** | **Quectel BC660K-GL** (pásma B1, B3, B5, B8, B20, B28), nanoSIM / eSIM slot |
| **Bezdrátové nabíjení** | **TI BQ51013BRHLR** – certifikovaný přijímač Qi v1.2 (až 5 W) |
| **Správa napájení a baterie** | **TI BQ24232RGTR** – lineární nabíječ Li-Ion/Li-Po s dynamickým Power-Path |
| **Napájení MCU větve** | **TI TPS62842DGRR** – ultra-low IQ synchronní step-down měnič ($I_Q \approx 60\text{ nA}$) |
| **Napájení modemu** | **TI TPS628502QDRLRQ1** – 2A synchronní step-down měnič dimenzovaný na proudové špičky NB-IoT |
| **Uživatelské rozhraní** | RGB LED stavová signalizace, piezoelektrický bzučák, servisní USB-C rozhraní |

---

## 6. Požadavky a otevření projektu

- **KiCad EDA:** Doporučena verze **8.0** nebo vyšší (projekt byl vytvořen a verifikován v KiCad 8/9).
- Pro otevření projektu otevřete soubor `DP-Kontrola.kicad_pro` v prostředí KiCad.
- Pro výrobu DPS jsou přímo v kořenové složce připraveny výrobní soubory Gerber (`DP-Kontrola-*.gbr`) a vrtací soubory Excellon (`*.drl`).
- Pro mechanickou integraci do pouzdra jsou k dispozici modely `DP-Kontrola-base.step` a `DP-Kontrola-lid.step`.

---

## 7. Vazby na další projekty

Projekt je pevnou součástí ekosystému diplomové práce:

- **[DP-Zavodnik](../DP-Zavodnik) (PRJ-11):** Párová mobilní jednotka závodníka, se kterou kontrola komunikuje protokolem 802.15.4.
- **[DP Monorepo](https://github.com/nagyjose/DP):** Centrální repozitář obsahující firmware obou jednotek (`Kontrola_Syst`, `Zavodnik_Syst`).
- **[DP-Panel](../../production) (PRJ-12):** Panelizovaná výrobní předloha sdružující desky Kontrola a Závodník do jednoho výrobního přířezu.
- **[DP-jigs](../../testing) (PRJ-13):** Jehličkový programovací a testovací přípravek (pogo-pin bed-of-nails) pro oživování této desky.
- **[DP-Enclosure](../../mechanics) (PRJ-15):** 3D model vodotěsného plastového pouzdra navržený ve FreeCADu.

---

## 8. Stav projektu a historie

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
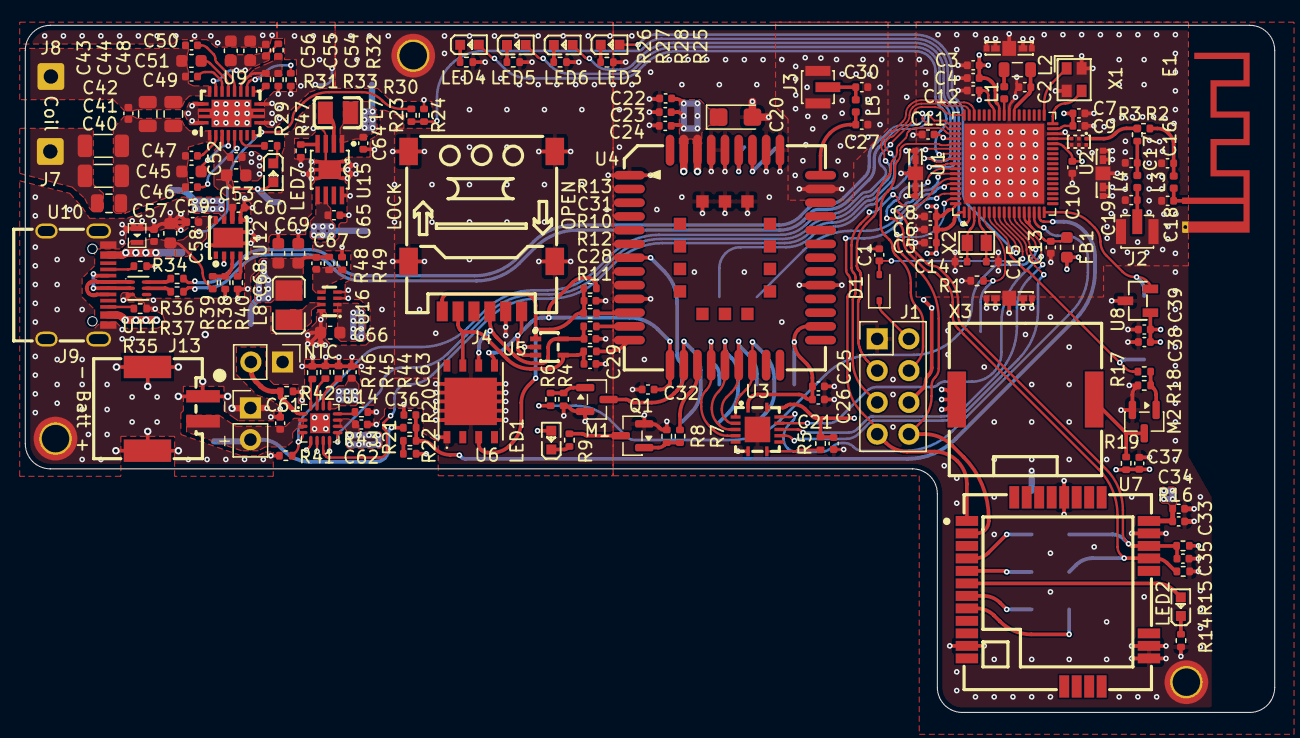
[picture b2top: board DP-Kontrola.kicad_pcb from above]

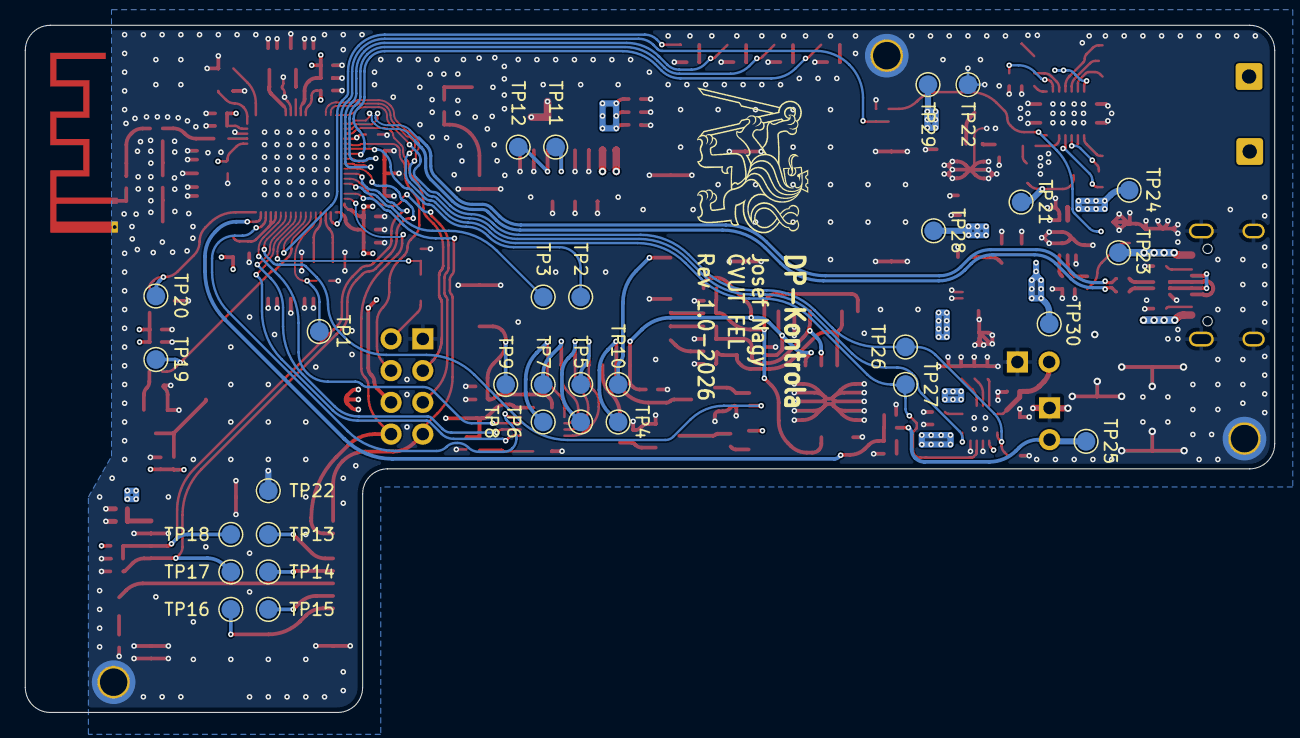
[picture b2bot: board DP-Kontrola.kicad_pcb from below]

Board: 4 copper layers, 100.0 x 55.0 mm, 204 parts (31 on the bottom side), 121 nets.

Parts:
C1, C4, C6, C7, C8, C10, C11, C12, C13, C21, C22, C25, C32, C34, C35, C36, C37, C39, C52, C54, C59, C60: 100n; C_0402_1005Metric
C2, C3, C5, C26, C33, C38, C61, C62, C63, C65: 4.7u; C_0402_1005Metric
C9, C23, C43, C57: 100p; C_0402_1005Metric
C14, C15: 7.5p; C_0402_1005Metric
C16, C17, C18, C19, C27, C30: N.C.; C_0402_1005Metric
C20: 100u; CP_EIA-3216-18_Kemet-A
C24: 22p; C_0402_1005Metric
C28, C29, C31: 33p; C_0402_1005Metric
C40, C48: N.C.; C_0805_2012Metric
C41, C42: 100n; C_1206_3216Metric
C44: 2.2n; C_0805_2012Metric
C45, C51: 470n; C_0603_1608Metric
C46, C50: 22n; C_0402_1005Metric
C47, C49: 10n; C_0402_1005Metric
C53, C55, C56, C66, C68, C69: 10u; C_0603_1608Metric
C58: 4.7u; C_0603_1608Metric
C64: 10u; C_0402_1005Metric
C67: 10p; C_0402_1005Metric
D1: 1N5819WS; D_SOD-323
E1: MIFA-2.45-GHz; Texas_SWRA117D_2.4GHz_Left
FB1: BLM18AG601SN1D; L_0603_1608Metric
H1, H2, H3: MountingHole_Pad; MountingHole_2.2mm_M2_ISO7380_Pad_TopBottom
J1: Conn_02x04_Counter_Clockwise; PinHeader_2x04_P2.54mm_Vertical
J2, J3: CONUFL001-SMD-T; IPEX-SMD_3P-L2.6-W2.6-LS3.0
J4: HYC240-SIM06-150; SIM-SMD_HYC240-SIM06-150
J7, J8: SolderWire-0.5sqmm_1x01_D0.9mm_OD2.1mm
J9: TYPE-C-31-M-12; USB-C_SMD-TYPE-C-31-M-12_1
J10, J11: Conn_01x02; PinHeader_1x02_P2.54mm_Vertical
J13: HX_SM02B-PASS-TB; CONN-TH_HX-SM02B-PASS-TB
L1: 10n; L_0402_1005Metric
L2: 10u; L_0805_2012Metric
L3, L4, L5: 0R; L_0402_1005Metric
L7: 2.2u; L0806
L8: 470n; L1008
LED1, LED5: VLMG1300-GS08; LED0603-RD_BLUE
LED2, LED4: VLMS1300-GS08; LED0603-RD_BLUE
LED3: VLMO1300-GS08; LED0603-RD_BLUE
LED6, LED7: VLMB1300-GS08; LED0603-RD_BLUE
M1, M2: 2N7002; SOT-23
Q1: MMBT3904; SOT-23
R1, R5, R6, R13, R15, R16, R18, R30, R41, R42: 10k; R_0402_1005Metric
R2, R3, R36, R37: 0R; R_0402_1005Metric
R4, R17: 100R; R_0402_1005Metric
R7: 4.7k; R_0402_1005Metric
R8: 47k; R_0402_1005Metric
R9, R14, R25, R26, R27, R28: 200R; R_0402_1005Metric
R10, R11, R12: 22R; R_0402_1005Metric
R19, R29: 1k; R_0402_1005Metric
R20, R21, R22: 1M; R_0402_1005Metric
R23, R24, R38: 100k; R_0402_1005Metric
R31: 330R; R_0402_1005Metric
R32: 20k; R_0402_1005Metric
R33: 196R; R_0402_1005Metric
R34, R35: 5.1k; R_0402_1005Metric
R39: 22k; R_0402_1005Metric
R40: 470R; R_0402_1005Metric
R43, R45: 3.09k; R_0402_1005Metric
R44: 68k; R_0402_1005Metric
R46: 1.74k; R_0402_1005Metric
R47: 52.3k; R_0402_1005Metric
R48: 88.7k; R_0402_1005Metric
R49: 19.6k; R_0402_1005Metric
SC1, SC2, SC3, SC4: S0951-46R; SMD_S0951-46R_1
TP1, TP2, TP3, TP4, TP5, TP6, TP7, TP8, TP9, TP10, TP11, TP12, TP13, TP14, TP15, TP16, TP17, TP18, TP19, TP20, TP21, TP22, TP22#2, TP23, TP24, TP25, TP26, TP27, TP28, TP29, TP30: TestPoint_Pad_D1.5mm
U1: STM32WB55RGVx; QFN-68-1EP_8x8mm_P0.4mm_EP6.4x6.4mm
U2: MLPF-WB55-01E3; FILTER-SMD_6P-L1.6-W1.0-P0.50-BL
U3: TXS0104ERGYR; VQFN-14_L3.5-W3.5-P0.50-BL-EP
U4: BC660KGLAA-I03-SNASA; LCC-LGA-58_L17.7-W15.8-P1.1-TL-BC260Y-CN
U5: ESDA6V1W5; SC-70-5_L2.1-W1.3-P0.65-LS2.1-BR
U6: MFF2; QFN-8_L6.0-W5.0-P1.27-TL-EP
U7: RAK3172-T-8-SM-I; WIRELM-SMD_32P-L15.5-W15.0-P1.00
U8: DRV5032FADBZR; SOT-23-3_L2.9-W1.3-P0.95-LS2.4-BR
U9: BQ51013BRHLR; VQFN-20_L4.5-W3.5-P0.50-BL-EP_BQ24100RHLR
U10: ESDA7P60-1U1M; D1610-RD
U11: ECMF02-2AMX6; UFQFN-6_L1.7-W1.5
U12: TPS2113ADRBR; SON-8_L3.0-W3.0-P0.65-LS3.0-BL-EP
U14: BQ24232RGTR; VQFN-16_L3.0-W3.0-P0.50-TL-EP
U15: TPS62842DGRR; HVSSOP-8_L3.0-W3.0-P0.65-LS4.9-BL-EP
U16: TPS628502QDRLRQ1; SOT-583-8_L2.1-W1.2-P0.50-LS1.6-BR
X1: NX2016SA-32MHZ-STD-CZS-5; OSC-SMD_4P-L2.0-W1.6-BL
X2: NX2012SA-32_768KHZ-EXS00A-MU00527; CRYSTAL-SMD_L2.0-W1.2
X3: PKLCS1212E4001-R1; BUZ-SMD_2P-L12.0-W12.0-L_PKLCS1212E4001-R1

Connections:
+3V3: C3.1, C4.1, C5.1, C6.1, C7.1, C8.1, C9.1, C10.1, C11.1, C12.1, C21.1, C38.1, C39.1, C64.1, FB1.1, J1.6, L7.1, R5.2, TP29.1, U1.1 (VBAT), U1.30 (VDD), U1.33 (VDDRF), U1.44 (VDDSMPS), U1.45 (VDD), U1.55 (VDDUSB), U1.68 (VDD), U3.14 (VCCB), U8.1 (VCC), U15.1 (VOS)
+4V: C62.1, C65.1, C66.1, TP28.1, U14.5 (EN2), U14.10 (OUT), U14.11 (OUT), U15.5 (EN), U15.6 (VIN), U16.1 (VIN), U16.2 (EN)
+5VD: C63.1, TP24.1, U12.7 (OUT), U14.13 (IN)
+5VL: C52.1, C53.1, C60.1, LED7.2 (+), TP21.1, U9.4 (OUT), U12.6 (IN2)
+5VP: C57.1, C58.1, C59.1, J9.A4B9 (VBUS), J9.B4A9 (VBUS), R23.2, R38.2, TP23.1, U9.9 (AD), U10.1 (C), U12.8 (IN1)
/BLE-RF/rf1: R2.1, R3.1, U2.1 (OUT)
/BLE-RF/rf2: C16.1, L3.1, R2.2
/BLE-RF/rf3: C18.1, E1.1 (FEED), L3.2
/BLE-RF/rf4: C17.1, L4.1, R3.2
/BLE-RF/rf5: C19.1, J2.1, L4.2
/LoRa-module/led4: LED2.2 (+), U7.6 (PA1)
/LoRa-module/led5: LED2.1 (-), R14.2
/LoRa-module/swclk: TP16.1, U7.8 (PA14/SWCLK)
/LoRa-module/swdio: TP15.1, U7.7 (PA13/SWDIO)
/LoRa-module/uart-rx: TP14.1, U7.5 (PB7/UART1_RX)
/LoRa-module/uart-tx: TP13.1, U7.4 (PB6/UART1_TX)
/MCU/smps: L1.1, L2.2
/NB-IoT-module/boot: TP10.1, U4.7 (BOOT)
/NB-IoT-module/dbg_rxd: TP12.1, U4.38 (DBG_RXD)
/NB-IoT-module/dbg_txd: TP11.1, U4.39 (DBG_TXD)
/NB-IoT-module/led1: Q1.1 (B), R7.1, R8.1
/NB-IoT-module/led2: Q1.3 (C), R9.1
/NB-IoT-module/led3: LED1.1 (-), R9.2
/NB-IoT-module/main_rxd: TP6.1, U3.4 (A3), U4.18 (MAIN_RXD)
/NB-IoT-module/main_txd: TP5.1, U3.5 (A4), U4.17 (MAIN_TXD)
/NB-IoT-module/oe: R5.1, U3.8 (OE)
/NB-IoT-module/psm_eint: TP7.1, U3.3 (A2), U4.19 (PSM_EINT)
/NB-IoT-module/res-g: M1.1 (G), R4.1, R6.2
/NB-IoT-module/rf6: C27.1, L5.1, U4.35 (ANT_RF)
/NB-IoT-module/rf7: C30.1, J3.1, L5.2
/NB-IoT-module/ri: TP8.1, U3.2 (A1), U4.20 (RI)
/NB-IoT-module/sim-c: C29.1, J4.C3 (CLK), R11.1, U5.4, U6.6 (CLOCK)
/NB-IoT-module/sim-d: C31.1, J4.C7 (I/O), R10.1, R13.2, U5.1, U6.3 (I/O)
/NB-IoT-module/sim-r: C28.1, J4.C2 (RST), R12.1, U5.5, U6.7 (RESET)
/NB-IoT-module/vdd_ext: C25.1, C26.1, TP9.1, U3.1 (VCCA), U4.24 (VDD_EXT)
/power-management/MCU-regulator/sw: L7.2, U15.2 (SW)
/power-management/MCU-regulator/vset: R47.2, U15.4 (VSET)
/power-management/USB-plug/cc1: J9.A5 (CC1), R34.2
/power-management/USB-plug/cc2: J9.B5 (CC2), R35.2
/power-management/USB-plug/d1+: J9.A6 (DP1), J9.B6 (DP2), U11.1 (D+)
/power-management/USB-plug/d1-: J9.A7 (DN1), J9.B7 (DN2), U11.2 (D-)
/power-management/USB-plug/d2+: R36.1, U11.6 (D+)
/power-management/USB-plug/d2-: R37.1, U11.5 (D-)
/power-management/battery-monitor/ilim3: R43.2, U14.12 (ILIM)
/power-management/battery-monitor/iset: R46.2, U14.16 (ISET)
/power-management/battery-monitor/iterm: R45.2, U14.15 (ITERM)
/power-management/battery-monitor/tmr: R44.2, U14.14 (TMR)
/power-management/battery-monitor/ts2: J11.2, R42.2, U14.1 (TS)
/power-management/module-regulator/fb: C67.2, R48.1, R49.2, U16.5 (FB)
/power-management/module-regulator/sw2: L8.1, U16.7 (SW)
/power-management/power-switch/ilim2: R40.2, U12.4 (ILIM)
/power-management/power-switch/vsns: R38.1, R39.2, U12.3 (VSNS)
/power-management/wireless-charger/ac1a: C40.1, C41.1, C42.1, J7.1
/power-management/wireless-charger/fod: R31.1, R32.1, R33.1, U9.14 (FOD)
/power-management/wireless-charger/ilim: R31.2, U9.12 (ILIM)
/power-management/wireless-charger/led6: LED7.1 (-), R29.2
/power-management/wireless-charger/led7: R29.1, U9.7 (/CHG)
/power-management/wireless-charger/rect: C54.1, C55.1, C56.1, R32.2, U9.18 (RECT)
/power-management/wireless-charger/ts-ctrl: R30.2, U9.13 (TS/CTRL)
/signaling/bz1: M2.1 (G), R17.1, R18.2
/signaling/bz2: M2.3 (D), R19.1, X3.2 (-)
/signaling/led8: LED3.1 (-), R25.2
/signaling/led9: LED4.1 (-), R26.2
/signaling/led10: LED5.1 (-), R27.2
/signaling/led11: LED6.1 (-), R28.2
/signaling/meas: R21.1, R22.2
AC1: C40.2, C41.2, C42.2, C43.1, C44.1, C45.1, C46.1, C47.1, C48.1, U9.2 (AC1)
AC2: C43.2, C44.2, C48.2, C49.1, C50.1, C51.1, J8.1, U9.19 (AC2)
BATT_MEAS: C36.1, R20.1, R21.2, U1.16 (ADC1_IN6)
BC660K_RESET_N: M1.3 (D), TP4.1, U4.15 (RESET_N)
BOOT1: C47.2, U9.3 (BOOT1)
BOOT2: C49.2, U9.17 (BOOT2)
CHRG_CE: R41.2, TP26.1, U1.51 (PA10), U14.4 (CE#)
CHRG_CHG: U1.49 (PB15), U14.9 (CHG#)
CHRG_PGOOD: TP27.1, U1.50 (PC6), U14.7 (PGOOD#)
CLAMP1: C45.2, U9.5 (CLMP1)
CLAMP2: C51.2, U9.16 (CLMP2)
COMM1: C46.2, U9.6 (COM1)
COMM2: C50.2, U9.15 (COM2)
GND: C1.2, C2.2, C3.2, C4.2, C5.2, C6.2, C7.2, C8.2, C9.2, C10.2, C11.2, C12.2, C13.2, C14.2, C15.2, C16.2, C17.2, C18.2, C19.2, C20.2, C21.2, C22.2, C23.2, C24.2, C25.2, C26.2, C27.2, C28.2, C29.2, C30.2, C31.2, C32.1, C33.2, C34.2, C35.2, C36.2, C37.2, C38.2, C39.2, C52.2, C53.2, C54.2, C55.2, C56.2, C57.2, C58.2, C59.2, C60.2, C61.2, C62.2, C63.2, C64.2, C65.2, C66.2, C68.2, C69.2, E1.2 (NC), H1.1, H2.1, H3.1, J1.1, J2.2, J2.3, J3.2, J3.3, J4.7 (EH), J4.8 (EH), J4.9 (EH), J4.10 (EH), J4.C5 (GND), J9.1 (EH), J9.2 (EH), J9.3 (EH), J9.4 (EH), J9.A1B12 (GND), J9.B1A12 (GND), J10.1, J11.1, J13.1, J13.3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
HAL_WKUP: TP20.1, U1.17 (SYS_WKUP4), U8.2 (OUT)
LoRa_BOOT: R15.2, TP17.1, U1.61 (PD0), U7.21 (BOOT0)
LoRa_RST: C35.1, R16.1, TP18.1, U1.62 (PD1), U7.22 (RST)
NBIoR_PSM_EINT: U1.12 (PC3), U3.12 (B2)
NBIoT_RESET_N: R4.2, U1.11 (PC2)
NBIoT_RI: U1.15 (SYS_WKUP1), U3.13 (B1)
NETLIGHT: R7.2, U4.16 (NETLIGHT)
unnamed: D1.1 (K), J1.2
SIG_Blink: LED3.2 (+), U1.7 (PB9)
SIG_Buzzer: R17.2, TP19.1, U1.6 (TIM16_CH1)
SIG_LED1: LED4.2 (+), U1.58 (PC10)
SIG_LED2: LED5.2 (+), U1.59 (PC11)
SIG_LED3: LED6.2 (+), U1.60 (PC12)
SRM32_JTRST: TP3.1, U1.64 (SYS_JTRST)
STM32_BOOT0: R1.2, TP1.1, U1.5 (PH3)
STM32_DN: R37.2, U1.52 (USB_DM)
STM32_DP: R36.2, U1.53 (USB_DP)
STM32_JTDI: TP2.1, U1.57 (SYS_JTDI)
STM32_JTDO: J1.5, U1.63 (SYS_JTDO-SWO)
STM32_NRST: C1.1, D1.2 (A), U1.8 (NRST)
STM32_OSC32_IN: C14.1, U1.3 (RCC_OSC32_IN), X2.1 (OSC1)
STM32_OSC32_OUT: C15.1, U1.4 (RCC_OSC32_OUT), X2.2 (OSC2)
STM32_OSC_IN: U1.35 (OSC_IN), X1.1
STM32_OSC_OUT: U1.34 (OSC_OUT), X1.3
STM32_RF1: U1.31 (RF1), U2.3 (IN)
STM32_RX-LoRa_TX: J1.8, U1.67 (USART1_RX), U7.2 (PA2/UART2_TX)
STM32_RX-NBIoT_TX: U1.9 (LPUART1_RX), U3.10 (B4)
STM32_SMPS_FB: C2.1, L2.1, U1.41 (VFBSMPS)
STM32_SMPS_LX: L1.2, U1.43 (VLXSMPS)
STM32_SWCLK: J1.4, U1.56 (SYS_JTCK-SWCLK)
STM32_SWDIO: J1.3, U1.54 (SYS_JTMS-SWDIO)
STM32_TX-LoRa_RX: J1.7, U1.66 (USART1_TX), U7.1 (PA3/UART2_RX)
STM32_TX-NBIoT_RX: U1.10 (LPUART1_TX), U3.11 (B3)
USB_TRIG: R23.1, R24.2, U1.2 (SYS_WKUP2)
USIM_CLK: R11.2, U4.13 (USIM_CLK)
USIM_DATA: R10.2, U4.11 (USIM_DATA)
USIM_RST: R12.2, U4.12 (USIM_RST)
USIM_VDD: C32.2, J4.C1 (VCC), R13.1, U4.14 (USIM_VDD), U5.3, U6.8 (VCC)
VBAT: C61.1, J10.2, J13.2, R20.2, TP25.1, U14.2 (BAT), U14.3 (BAT)
VDD: C20.1, C22.1, C23.1, C24.1, C33.1, C34.1, C37.1, C67.1, C68.1, C69.1, L8.2, LED1.2 (+), R16.2, R19.2, R48.2, TP30.1, U4.42 (VBAT), U4.43 (VBAT), U7.24 (VDD), X3.1 (+)
VDDA: C13.1, FB1.2, U1.13 (VREF+), U1.14 (VDDA)
